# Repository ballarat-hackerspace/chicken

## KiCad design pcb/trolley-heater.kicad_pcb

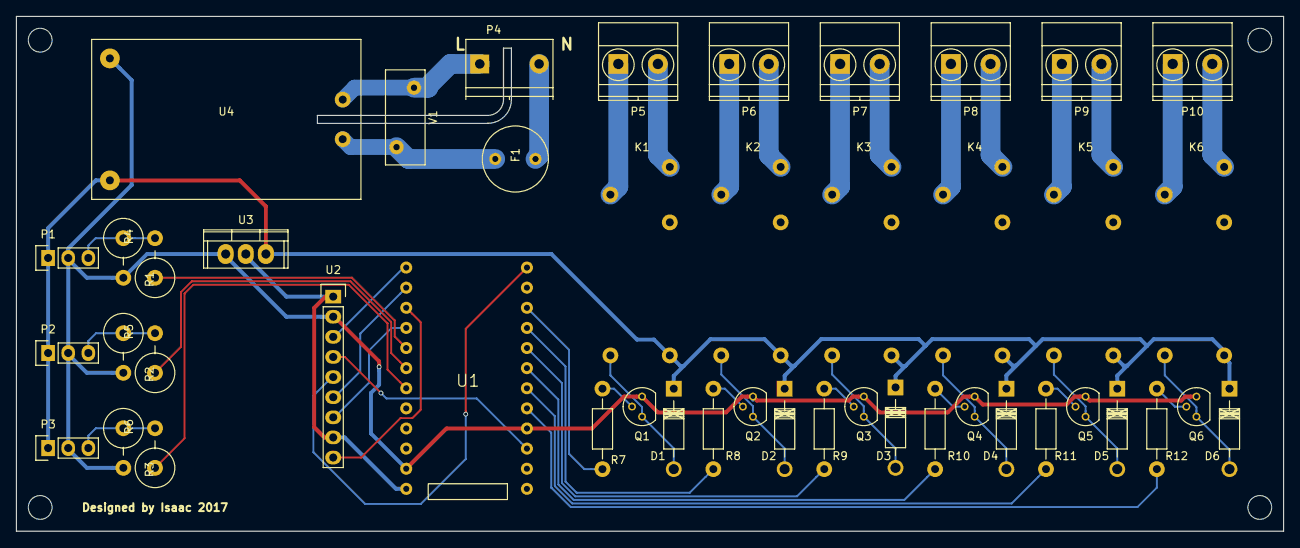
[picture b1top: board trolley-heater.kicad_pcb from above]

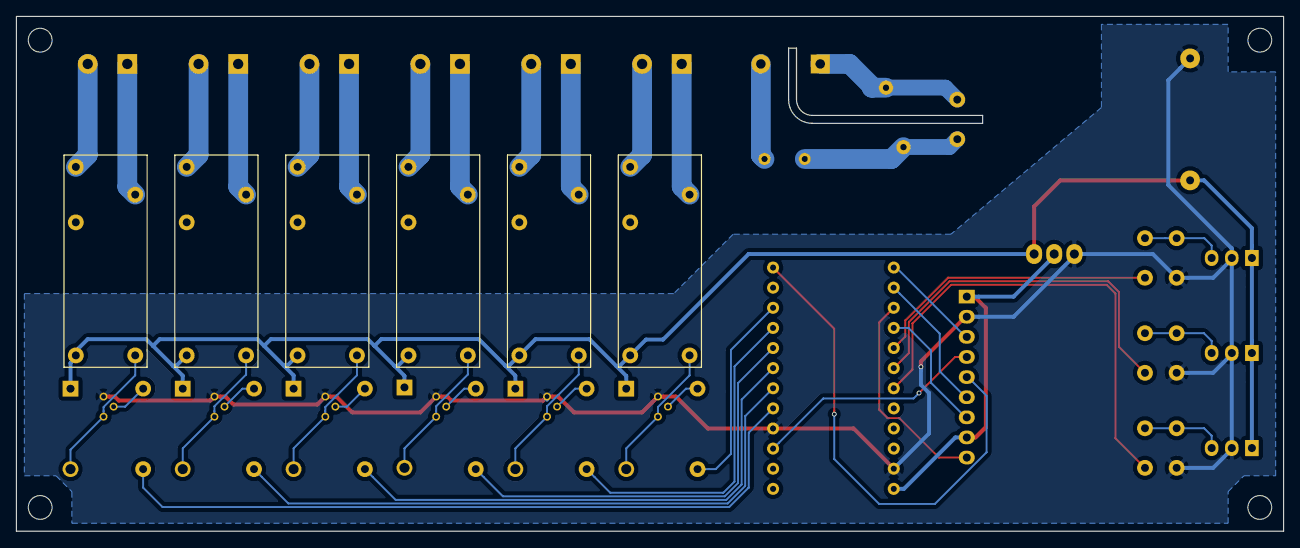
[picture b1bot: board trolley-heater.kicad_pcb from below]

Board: 2 copper layers, 160.0 x 65.0 mm, 50 parts (6 on the bottom side), 48 nets.

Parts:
D1, D2, D3, D4, D5, D6: D_Small; Diode_DO-41_SOD81_Horizontal_RM10
F1: 0.8A; Fuse_Radial
K1, K2, K3, K4, K5, K6: RELAY_SPDT
MH1, MH2, MH3, MH4: MountingHole_3mm
P1, P2, P3: CONN_01X03; Pin_Header_Straight_1x03
P4: CONN_01X02; TerminalBlock_Pheonix_PT-7.5mm_2pol
P5, P6, P7, P8, P9, P10: CONN_01X02; TerminalBlock_Pheonix_MKDS1.5-2pol
Q1, Q2, Q3, Q4, Q5, Q6: Q_NPN_CBE; TO-92_Molded_Narrow
R1, R2, R3: 2k2; Resistor_Vertical_RM5mm
R4, R5, R6: 1k; Resistor_Vertical_RM5mm
R7, R8, R9, R10, R11, R12: 1k; Resistor_Horizontal_RM10mm
U1: ARDUPROMINI; ArduProMini-6
U2: SPITFTSD; Pin_Header_Straight_1x09
U3: LM1084IT-3.3/NOPB; TO-220
U4: HLK-PM01
V1: 275V; RV_Disc_D12_W5_P7.5

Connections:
+3V3: U1.30, U2.1, U2.8, U3.2
+5V: D1.1, D2.1, D3.1, D4.1, D5.1, D6.1, K1.1, K2.1, K3.1, K4.1, K5.1, K6.1, P1.1, P2.1, P3.1, U3.3, U4.3
/CH1_IN: R4.1, U1.23
/CH1_OUT: R7.2, U1.16
/CH2_IN: R5.1, U1.24
/CH2_OUT: R10.2, U1.13
/CH3_IN: R6.1, U1.25
/CH3_OUT: R8.2, U1.15
/CH4_OUT: R11.2, U1.12
/CH5_OUT: R9.2, U1.14
/CH6_OUT: R12.2, U1.11
/CS: U1.19, U2.3
/D/C: U1.18, U2.5
/MISO: U1.21, U2.9
/MOSI: U1.20, U2.6
/RST: U1.9, U2.4
/SCLK: U1.22, U2.7
GNDREF: P1.2, P2.2, P3.2, Q1.3, Q2.3, Q3.3, Q4.3, Q5.3, Q6.3, R1.2, R2.2, R3.2, U1.10, U1.29, U2.2, U3.1, U4.4
unnamed: D1.2, K1.2, Q1.1
unnamed: D2.2, K2.2, Q2.1
unnamed: D3.2, K3.2, Q3.1
unnamed: D4.2, K4.2, Q4.1
unnamed: D5.2, K5.2, Q5.1
unnamed: D6.2, K6.2, Q6.1
unnamed: F1.1, P4.2
unnamed: F1.2, U4.1, V1.1
unnamed: K1.11, P5.1
unnamed: K1.14, P5.2
unnamed: K2.11, P6.1
unnamed: K2.14, P6.2
unnamed: K3.11, P7.1
unnamed: K3.14, P7.2
unnamed: K4.11, P8.1
unnamed: K4.14, P8.2
unnamed: K5.11, P9.1
unnamed: K5.14, P9.2
unnamed: K6.11, P10.1
unnamed: K6.14, P10.2
unnamed: P1.3, R1.1, R4.2
unnamed: P2.3, R2.1, R5.2
unnamed: P3.3, R3.1, R6.2
unnamed: P4.1, U4.2, V1.2
unnamed: Q1.2, R7.1
unnamed: Q2.2, R8.1
unnamed: Q3.2, R9.1
unnamed: Q4.2, R10.1
unnamed: Q5.2, R11.1
unnamed: Q6.2, R12.1

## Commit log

2017-01-21 initial commit.
2017-01-24 removed: auto generated files.
2017-01-24 updated: prepare for 1.0 release.
2017-01-24 updated: with fill and additional mains filtering.
2017-01-24 updated: tweaking ac input connector and battery pack support.
